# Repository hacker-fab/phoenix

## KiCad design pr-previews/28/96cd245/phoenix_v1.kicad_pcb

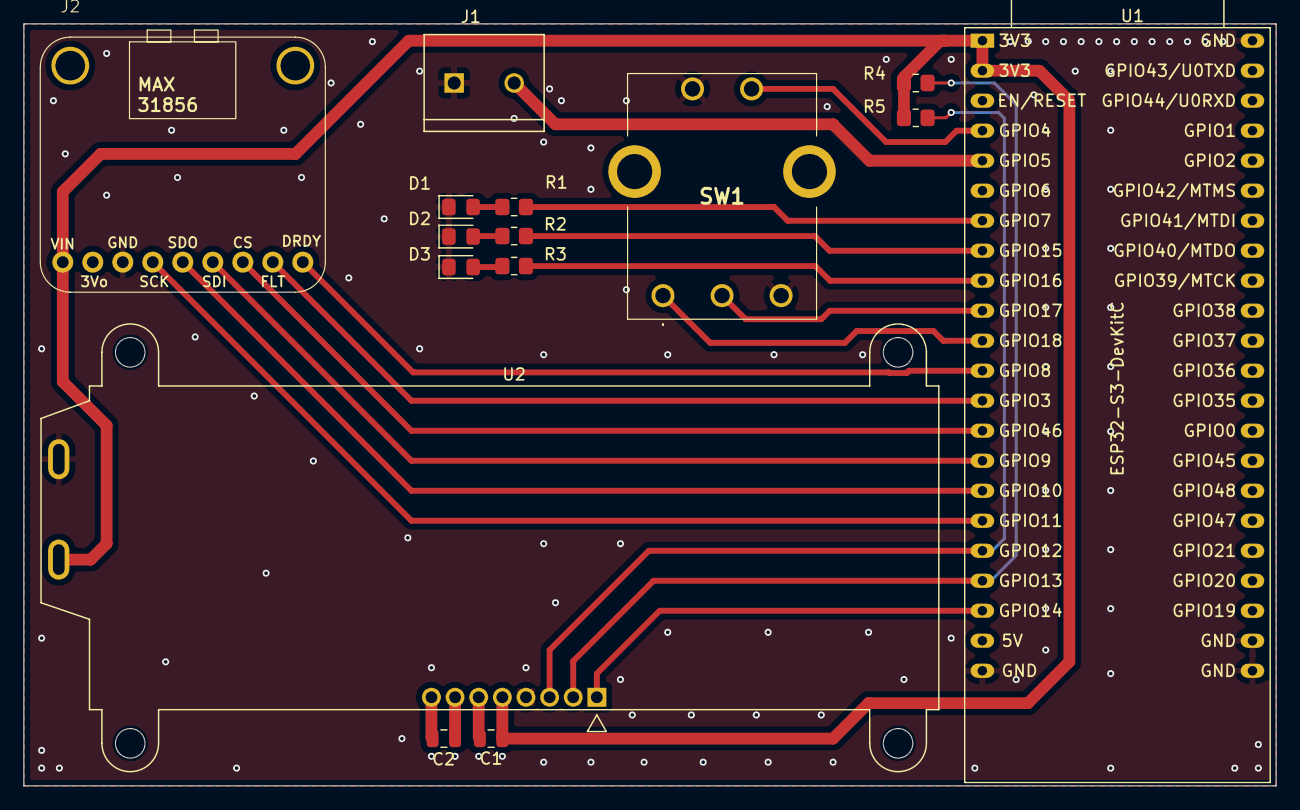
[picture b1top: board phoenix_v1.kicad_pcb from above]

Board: 2 copper layers, 106.0 x 64.5 mm, 15 parts (0 on the bottom side), 24 nets.

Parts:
C1, C2: 1uF; C_0805_2012Metric
D1, D2, D3: LED; D_0805_2012Metric_Pad1.15x1.40mm_HandSolder
J1: Screw_Terminal_01x02; TE_282837-2
J2: Conn_01x09_Socket; MAX31856_HEADER
R1, R2, R3: 220; R_0805_2012Metric_Pad1.20x1.40mm_HandSolder
R4, R5: 4.7k; R_0805_2012Metric_Pad1.20x1.40mm_HandSolder
SW1: RotaryEncoder_Switch; PEC164120FS0012
U1: ESP32-S3-DevKitC
U2: NHD-C0220BIZ; NHD-C0220BiZ

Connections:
+3.3V: C1.1, J2.9, R4.1, R5.1, U1.1 (3V3), U1.2 (3V3), U2.5 (VDD), U2.9 (A)
/DISPLAY_RST: U1.20 (GPIO14/ADC2_CH3), U2.1 (~RST)
/ENC_A: SW1.A, U1.11 (GPIO18/ADC2_CH7)
/ENC_B: SW1.B, U1.10 (GPIO17/ADC2_CH6)
/ENC_SW: SW1.S2, U1.4 (GPIO4/ADC1_CH3)
/LED_1: R1.1, U1.7 (GPIO7/ADC1_CH6)
/LED_2: R2.1, U1.8 (GPIO15/ADC2_CH4/32K_P)
/LED_3: R3.1, U1.9 (GPIO16/ADC2_CH5/32K_N)
/MAX_CS: J2.3, U1.14 (GPIO46)
/MAX_DRDY: J2.1, U1.12 (GPIO8/ADC1_CH7)
/MAX_FAULT: J2.2, U1.13 (GPIO3/ADC1_CH2)
/MAX_SCK: J2.6, U1.17 (GPIO11/ADC2_CH0)
/MAX_SDI: J2.4, U1.15 (GPIO9/ADC1_CH8)
/MAX_SDO: J2.5, U1.16 (GPIO10/ADC1_CH9)
/SCL: R4.2, U1.19 (GPIO13/ADC2_CH2), U2.2 (SCL)
/SDA: R5.2, U1.18 (GPIO12/ADC2_CH1), U2.3 (SDA)
/SSR_PWM: J1.2, U1.5 (GPIO5/ADC1_CH4)
GND: D1.1 (K), D2.1 (K), D3.1 (K), J1.1, J2.7, SW1.C, SW1.S1, U1.22 (GND), U1.23 (GND), U1.24 (GND), U1.44 (GND), U2.4 (VSS), U2.10 (K)
unnamed: D1.2 (A), R1.2
unnamed: D2.2 (A), R2.2
unnamed: D3.2 (A), R3.2
unnamed: C2.1, U2.7 (C1+)
unnamed: C2.2, U2.8 (C1-)
unnamed: C1.2, U2.6 (VOUT)
